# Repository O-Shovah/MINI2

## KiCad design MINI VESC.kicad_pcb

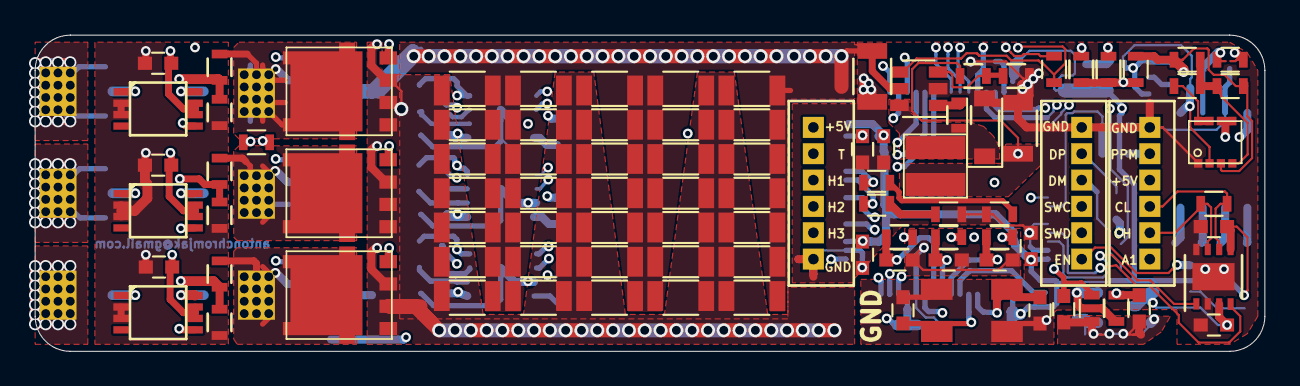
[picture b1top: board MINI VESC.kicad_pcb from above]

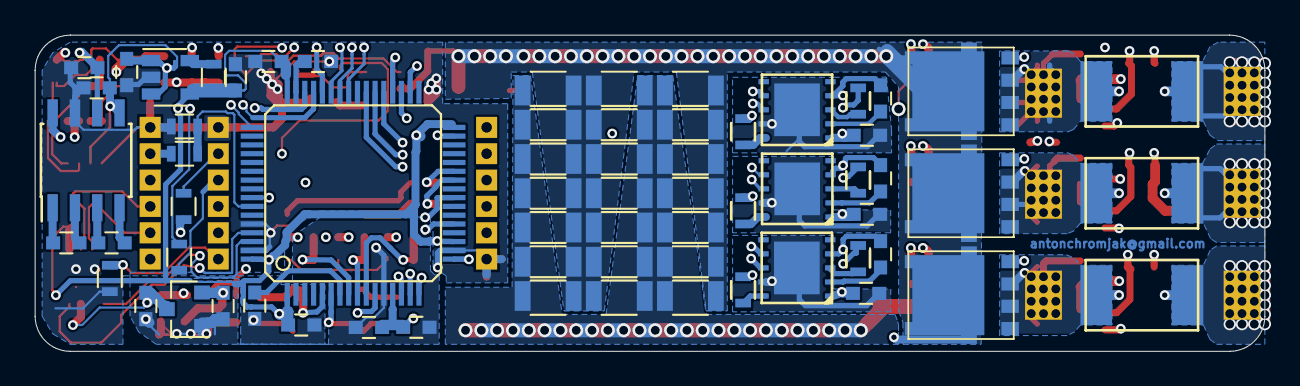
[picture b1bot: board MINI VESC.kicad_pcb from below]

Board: 4 copper layers, 70.0 x 18.0 mm, 168 parts (66 on the bottom side), 84 nets.

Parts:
C1, C2, C3: 220n; C_0603
C4, C5, C12, C13, C24, C25, C28, C32, C39, C48, C60, C61, C62, C63, C74, C75, C79, C82, C84, C85: 10u; R_1206
C6, C7, C8, C9, C10, C11, C17, C18, C19, C21, C22, C26, C27, C29, C77, C78, C86, C87, C88, C89, C90, C91, C92, C93, C94, C95, C96: 2u2; C_0603
C14, C15, C16: 4n7; C_0603
C20: 220nF; C_0603
C23: 220nF; R_0603
C30, C31: 10pF; C_0603
C33, C34, C35, C36, C37, C38, C40, C41, C42, C43, C44, C45, C46, C47, C49, C50, C51, C52, C53, C54, C55, C56, C57, C58, C59, C64, C65, C66, C67, C68, C69, C70, C71, C72, C73, C80, C81, C83: C; R_1206
C76: 100n; R_0603
D1: D_Schottky; D_SOD-123
D2: D_Zener; R_0603
D3, D4: LED; R_0603
L1: 22uH; WE-MAPI
L2: 2.2uH; R_0603
P1, P2, P3, P4, P5, P6: CONN_1; prekov
P9, P10, P11: CONN_01X06; JST_ZH_1.5_6-Pin
Q1, Q2, Q3, Q4, Q5, Q6: Q_NMOS_GSD; DFN5
Q7: Q8M51TR-E; TSMT8
R1, R2, R3: RSENS; 2512Rv2
R4, R12, R14, R16, R36: 25k5; R_0603
R5, R13, R15, R17: 2k2; R_0603
R6, R7, R8, R9, R10, R11, R23, R24, R35: 7R5; R_0603
R18, R19, R20, R30, R37: 100R; R_0603
R21: 510R; R_0603
R22: 8k; R_0603
R25, R27: 22R; R_0603
R26, R31, R33, R34: 10k; R_0603
R28, R29: 220R; R_0603
R32: 10kNTC; R_0603
U1, U2, U3: LM5001; WSON10__
U4, U5, U6: AD8418; MSOP
U7: STM32F40X_LQFP64; lqfp64_pad_mod
U8: LMR16006; SOT-23-6
U9: LM3671; SOT-23-5
U10: MCP1700; SOT-23
U11: MAX662; SOIC-8_3.9x4.9mm_Pitch1.27mm
U12: TJA1051TK/3; DFN-8-1EP_3x3mm_Pitch0.65mm
X1: CRYSTAL_SMD; 5x3.2KRISTALL

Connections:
+5V: C25.2, C87.1, C89.1, C91.1, C96.1, L1.2, P9.1, P11.4, Q7.2, R22.1, U9.1, U9.3, U10.3, U11.5, U12.3
+12V: C6.1, C7.1, C8.1, R37.2, U1.1, U2.1, U3.1
ADC_EXT1: P11.1, U7.21
C1: C14.2, R18.2, U7.8
C2: C15.2, R19.2, U7.9
C3: C16.2, R20.2, U7.10
CANH: P11.2, R35.1, U12.7
CANL: P11.3, R35.2, U12.6
DRIVER: U7.57, U11.8
EN: P10.1, R26.2, R33.2, U8.4
HALL_1: P9.3, U7.37
HALL_2: P9.4, U7.38
HALL_3: P9.5, U7.39
HI1: U1.7, U7.41
HI2: U2.7, U7.42
HI3: U3.7, U7.43
I1: R18.1, U4.5
I2: R19.1, U5.5
I3: R20.1, U6.5
LED_GREEN: D3.2, U7.26
LED_RED: D4.2, U7.27
LI1: U1.8, U7.34
LI2: U2.8, U7.35
LI3: U3.8, U7.36
unnamed: C1.1, U1.2
unnamed: C2.1, U2.2
unnamed: C3.1, U3.2
unnamed: C17.2, U7.31
unnamed: C18.2, U7.47
unnamed: C20.2, U7.7
unnamed: C23.1, D1.1, L1.1, U8.6
unnamed: C23.2, U8.1
unnamed: C30.1, U7.5, X1.1
unnamed: C31.1, U7.6, X1.2
unnamed: C77.2, R31.2, R32.2, U7.17
unnamed: C92.1, U11.2
unnamed: C92.2, U11.1
unnamed: C93.1, U11.3
unnamed: C93.2, U11.4
unnamed: C94.1, R37.1, U11.6
unnamed: D2.2, Q7.4, R23.1, R24.1
unnamed: D3.1, R29.2
unnamed: D4.1, R28.2
unnamed: L2.1, U9.5
unnamed: P1.1, R1.1, U4.1
unnamed: P2.1, R2.1, U5.1
unnamed: P3.1, R3.1, U6.1
unnamed: P10.4, R25.1
unnamed: P10.5, R27.1
unnamed: Q1.1, R6.1
unnamed: Q2.1, R7.2
unnamed: Q3.1, R8.1
unnamed: Q4.1, R9.2
unnamed: Q5.1, R10.1
unnamed: Q6.1, R11.2
unnamed: Q7.5, Q7.6, R4.1
unnamed: Q7.7, Q7.8, R23.2
unnamed: R6.2, U1.3
unnamed: R7.1, U1.10
unnamed: R8.2, U2.3
unnamed: R9.1, U2.10
unnamed: R10.2, U3.3
unnamed: R11.1, U3.10
unnamed: R21.2, R22.2, U8.3
RXC: U7.61, U12.4
SENS_1: R12.1, R13.2, U7.14
SENS_2: R14.1, R15.2, U7.15
SENS_3: R16.1, R17.2, U7.16
SENS_SUPPLY: R4.2, R5.2, R36.2, U7.11
SERVO: C76.2, R30.2, U7.58
SH1: C1.2, P4.1, Q1.2, Q2.3, R1.2, R12.2, U1.4, U4.8
SH2: C2.2, P5.1, Q3.2, Q4.3, R2.2, R14.2, U2.4, U5.8
SH3: C3.2, P6.1, Q5.2, Q6.3, R3.2, R16.2, U3.4, U6.8
SWCLK: P10.3, U7.49
SWDIO: P10.2, U7.46
TEMP_MOTOR: C78.2, P9.2, R34.2, U7.24
TXC: U7.62, U12.1
USB-DM: R25.2, U7.44
USB-DP: R27.2, U7.45
VAA: C9.2, C10.2, C11.2, C19.1, C86.1, C90.1, R32.1, R34.1, U4.6, U4.7, U5.6, U5.7, U6.6, U6.7, U7.13, U10.2
VCC: C21.1, C22.1, C26.1, C27.1, C29.1, C88.1, C95.1, L2.2, U7.1, U7.19, U7.32, U7.48, U7.64, U9.4, U12.5
VDD: C4.1, C5.1, C12.1, C13.1, C24.2, C28.1, C32.1, C33.1, C34.1, C35.1, C36.1, C37.1, C38.1, C39.1, C40.1, C41.1, C42.1, C43.1, C44.1, C45.1, C46.1, C47.1, C48.1, C49.1, C50.1, C51.1, C52.1, C53.1, C54.1, C55.1, C56.1, C57.1, C58.1, C59.1, C60.1, C61.1, C62.1, C63.1, C64.1, C65.1, C66.1, C67.1, C68.1, C69.1, C70.1, C71.1, C72.1, C73.1, C74.1, C75.1, C79.1, C80.1, C81.1, C82.1, C83.1, C84.1, C85.1, D2.1, Q1.3, Q3.3, Q5.3, Q7.3, R24.2, R33.1, R36.1, U8.5
VSS: C4.2, C5.2, C6.2, C7.2, C8.2, C9.1, C10.1, C11.1, C12.2, C13.2, C14.1, C15.1, C16.1, C17.1, C18.1, C19.2, C20.1, C21.2, C22.2, C24.1, C25.1, C26.2, C27.2, C28.2, C29.2, C30.2, C31.2, C32.2, C33.2, C34.2, C35.2, C36.2, C37.2, C38.2, C39.2, C40.2, C41.2, C42.2, C43.2, C44.2, C45.2, C46.2, C47.2, C48.2, C49.2, C50.2, C51.2, C52.2, C53.2, C54.2, C55.2, C56.2, C57.2, C58.2, C59.2, C60.2, C61.2, C62.2, C63.2, C64.2, C65.2, C66.2, C67.2, C68.2, C69.2, C70.2, C71.2, C72.2, C73.2, C74.2, C75.2, C76.1, C77.1, C78.1, C79.2, C80.2, C81.2, C82.2, C83.2, C84.2, C85.2, C86.2, C87.2, C88.2, C89.2, C90.2, C91.2, C94.2, C95.2, C96.2, D1.2, P9.6, P10.6, P11.6, Q2.2, Q4.2, Q6.2, Q7.1, R5.1, R13.1, R15.1, R17.1, R21.1, R26.1, R28.1, R29.1, R31.1, U1.9, U2.9, U3.9, U4.2, U4.3, U5.2, U5.3, U6.2, U6.3, U7.12, U7.18, U7.60, U7.63, U8.2, U9.2, U10.1, U11.7, U12.2, U12.8, U12.9, X1.3
servoi: P11.5, R30.1

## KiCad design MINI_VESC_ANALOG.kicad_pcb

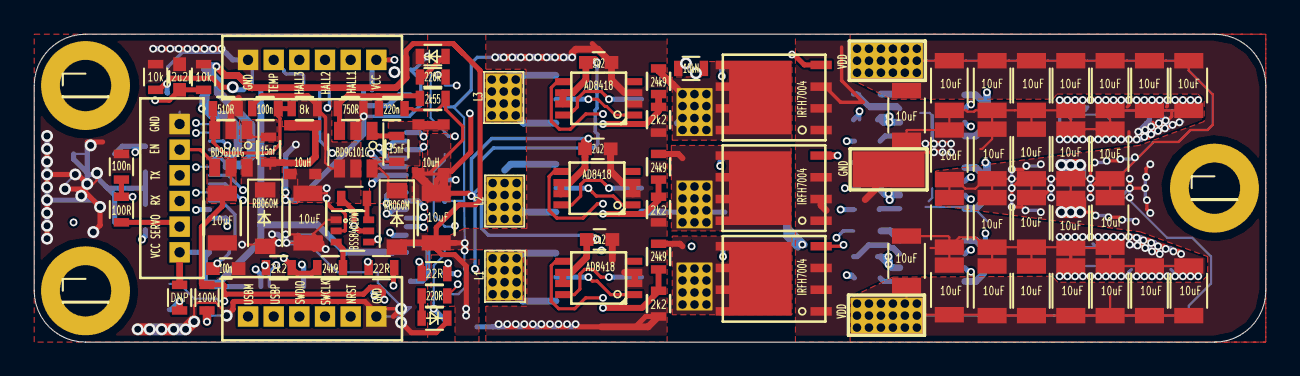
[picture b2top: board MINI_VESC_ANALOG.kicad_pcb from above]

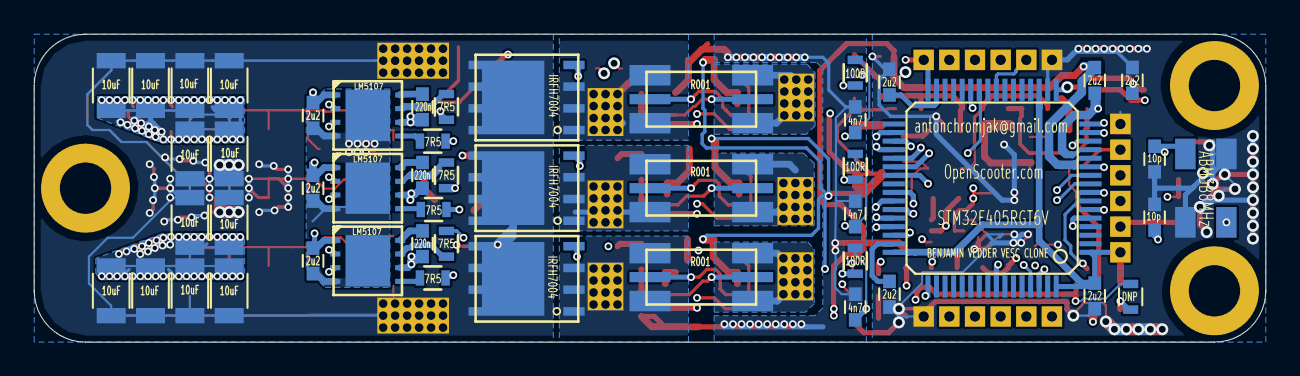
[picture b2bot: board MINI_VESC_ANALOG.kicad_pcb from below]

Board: 4 copper layers, 72.0 x 18.0 mm, 138 parts (49 on the bottom side), 81 nets.

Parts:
C1, C2, C3: 220n; C_0603
C4, C5, C12, C13, C24, C25, C29, C48: 10u; R_1206
C6, C7, C8, C9, C10, C11, C17, C18, C19, C21, C77, C78: 2u2; C_0603
C14, C15, C16: 4n7; C_0603
C20: 100n; C_0603
C22, C76: 100n; R_0603
C23, C27: C; R_0603
C26: 220n; R_0603
C30, C31: 18p; C_0603
C33, C34, C37, C38, C40, C41, C42, C43, C44, C45, C46, C47, C49, C50, C51, C52, C53, C54, C55, C56, C57, C58, C59, C64, C65, C66, C67, C68, C69, C70, C71, C72, C73: C; R_1206
D1, D2: D_Schottky; D_SOD-123
D3, D4: LED; R_0603
L1, L2: PFD3215
P1, P2, P3, P4, P5, P6, P7, P8, P12: CONN_1; prekov
P9, P10, P11: CONN_01X06; JST_ZH_1.5_6-Pin
Q1, Q2, Q3, Q4, Q5, Q6: Q_NMOS_GSD; PQFN5x6B
R1, R2, R3: RSENS; 2512Rv1
R4, R12, R14, R16: 25k5; R_0603
R5, R13, R15, R17, R35, R36: 2k2; R_0603
R6, R7, R8, R9, R10, R11: 7R5; R_0603
R18, R19, R20, R30: 100R; R_0603
R21: 510R; R_0603
R22: 8k; R_0603
R23: 750R; R_0603
R24: 2k55; R_0603
R25, R27: 22R; R_0603
R26, R31, R33, R34: 10k; R_0603
R28, R29: 220R; R_0603
R32: 10kNTC; R_0603
U1, U2, U3: LM5107; WSON
U4, U5, U6: AD8418; MSOP
U7: STM32F40X_LQFP64; lqfp64_pad_mod
U8, U9: BD9G101G; SOT-23-6
U10: 2xfet; SOT-363_SC-70-6
X1: CRYSTAL_SMD; 5x3.2KRISTALL

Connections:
+9V: C6.1, C7.1, C8.1, C22.1, C25.2, L1.1, L1.4, R22.1, U1.1, U2.1, U3.1, U9.4, U9.5, U10.2
C1: C14.2, R18.2, U7.8
C2: C15.2, R19.2, U7.9
C3: C16.2, R20.2, U7.10
EN: P11.5, R26.2, R33.2, U8.4
HALL_1: P9.2, U7.37
HALL_2: P9.3, U7.38
HALL_3: P9.4, U7.39
HI1: U1.2, U7.41
HI2: U2.2, U7.42
HI3: U3.2, U7.43
I1: R18.1, U4.5
I2: R19.1, U5.5
I3: R20.1, U6.5
LED_GREEN: D3.2, U7.26
LED_RED: D4.2, U7.27
LI1: U1.3, U7.34
LI2: U2.3, U7.35
LI3: U3.3, U7.36
NRST: C20.2, P10.5, U7.7
unnamed: C1.1, U1.8
unnamed: C2.1, U2.8
unnamed: C3.1, U3.8
unnamed: C17.2, U7.31
unnamed: C18.2, U7.47
unnamed: C22.2, R21.2, R22.2, U8.3
unnamed: C23.1, D1.1, L1.2, L1.3, U8.6
unnamed: C23.2, U8.1
unnamed: C26.2, R23.2, R24.2, U9.3
unnamed: C27.1, D2.1, L2.2, L2.3, U9.6
unnamed: C27.2, U9.1
unnamed: C30.1, U7.5, X1.1
unnamed: C31.1, U7.6, X1.2
unnamed: C77.2, R31.2, R32.2, U7.17
unnamed: D3.1, R29.2
unnamed: D4.1, R28.2
unnamed: P1.1, R1.1
unnamed: P2.1, R2.1
unnamed: P3.1, R3.1
unnamed: P10.1, R25.1
unnamed: P10.2, R27.1
unnamed: Q1.1, R6.1
unnamed: Q2.1, R7.1
unnamed: Q3.1, R8.1
unnamed: Q4.1, R9.1
unnamed: Q5.1, R10.1
unnamed: Q6.1, R11.1
unnamed: R1.3, U4.1
unnamed: R1.4, U4.8
unnamed: R2.3, U5.1
unnamed: R2.4, U5.8
unnamed: R3.3, U6.1
unnamed: R3.4, U6.8
unnamed: R4.2, U10.3
unnamed: R6.2, U1.7
unnamed: R7.2, U1.5
unnamed: R8.2, U2.7
unnamed: R9.2, U2.5
unnamed: R10.2, U3.7
unnamed: R11.2, U3.5
unnamed: R35.1, U10.6
unnamed: R35.2, R36.2, U10.5
RX: P11.3, U7.61
SENS_1: R12.1, R13.2, U7.14
SENS_2: R14.1, R15.2, U7.15
SENS_3: R16.1, R17.2, U7.16
SENS_SUPPLY: R4.1, R5.2, U7.11
SERVO: C76.2, R30.2, U7.57
SH1: C1.2, P4.1, Q1.2, Q2.3, R1.2, R12.2, U1.6
SH2: C2.2, P5.1, Q3.2, Q4.3, R2.2, R14.2, U2.6
SH3: C3.2, P6.1, Q5.2, Q6.3, R3.2, R16.2, U3.6
SWCLK: P10.4, U7.49
SWDIO: P10.3, U7.46
TEMP_MOTOR: C78.2, P9.5, R34.2, U7.24
TX: P11.4, U7.62
USB-DM: R25.2, U7.44
USB-DP: R27.2, U7.45
VCC: C9.2, C10.2, C11.2, C19.1, C21.1, C26.1, C29.2, L2.1, L2.4, P9.1, P11.1, R24.1, R26.1, R32.1, U4.6, U4.7, U5.6, U5.7, U6.6, U6.7, U7.1, U7.13, U7.19, U7.32, U7.48, U7.64
VDD: C4.1, C5.1, C12.1, C13.1, C24.2, C33.1, C34.1, C37.1, C38.1, C40.1, C41.1, C42.1, C43.1, C44.1, C45.1, C46.1, C47.1, C48.1, C49.1, C50.1, C51.1, C52.1, C53.1, C54.1, C55.1, C56.1, C57.1, C58.1, C59.1, C64.1, C65.1, C66.1, C67.1, C68.1, C69.1, C70.1, C71.1, C72.1, C73.1, P7.1, P8.1, Q1.3, Q3.3, Q5.3, R33.1, R36.1, U8.5, U10.4
VSS: C4.2, C5.2, C6.2, C7.2, C8.2, C9.1, C10.1, C11.1, C12.2, C13.2, C14.1, C15.1, C16.1, C17.1, C18.1, C19.2, C20.1, C21.2, C24.1, C25.1, C29.1, C30.2, C31.2, C33.2, C34.2, C37.2, C38.2, C40.2, C41.2, C42.2, C43.2, C44.2, C45.2, C46.2, C47.2, C48.2, C49.2, C50.2, C51.2, C52.2, C53.2, C54.2, C55.2, C56.2, C57.2, C58.2, C59.2, C64.2, C65.2, C66.2, C67.2, C68.2, C69.2, C70.2, C71.2, C72.2, C73.2, C76.1, C77.1, C78.1, D1.2, D2.2, P9.6, P10.6, P11.6, P12.1, Q2.2, Q4.2, Q6.2, R5.1, R13.1, R15.1, R17.1, R21.1, R23.1, R28.1, R29.1, R31.1, R34.1, U1.4, U2.4, U3.4, U4.2, U4.3, U5.2, U5.3, U6.2, U6.3, U7.12, U7.18, U7.60, U7.63, U8.2, U9.2, U10.1, X1.3
servoi: P11.2, R30.1
